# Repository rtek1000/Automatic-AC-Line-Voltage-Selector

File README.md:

# Automatic-AC-Line-Voltage-Selector
Automatic selector for 110VAC or 220VAC

- Usable for equipment that works with only 110V (to protect against wrong connection to 220V) or for 110V / 220V devices with manual switch selection.
- - It can operate with only 1 relay, but the 47V zener diode (D4, D5) must be kept in the scheme so as not to force the MOSFET (Q2).
-
- Operating mode is simple: the normally closed contact (NC) is for higher voltage connection (220V), when the AC line voltage is about 140Vac or less, the relay is activated.
- - The circuit has no hysteresis, so it may oscillate if the AC line voltage is at the threshold.
-
- Note: The wire colors in the example are merely illustrative:

Schematic:

Board:

## Licence:
- Hardware:

Released under CERN OHL 1.2: https://ohwr.org/cernohl

- This library is distributed in the hope that it will be useful, but WITHOUT ANY WARRANTY; without even the implied warranty of MERCHANTABILITY or FITNESS FOR A PARTICULAR PURPOSE.

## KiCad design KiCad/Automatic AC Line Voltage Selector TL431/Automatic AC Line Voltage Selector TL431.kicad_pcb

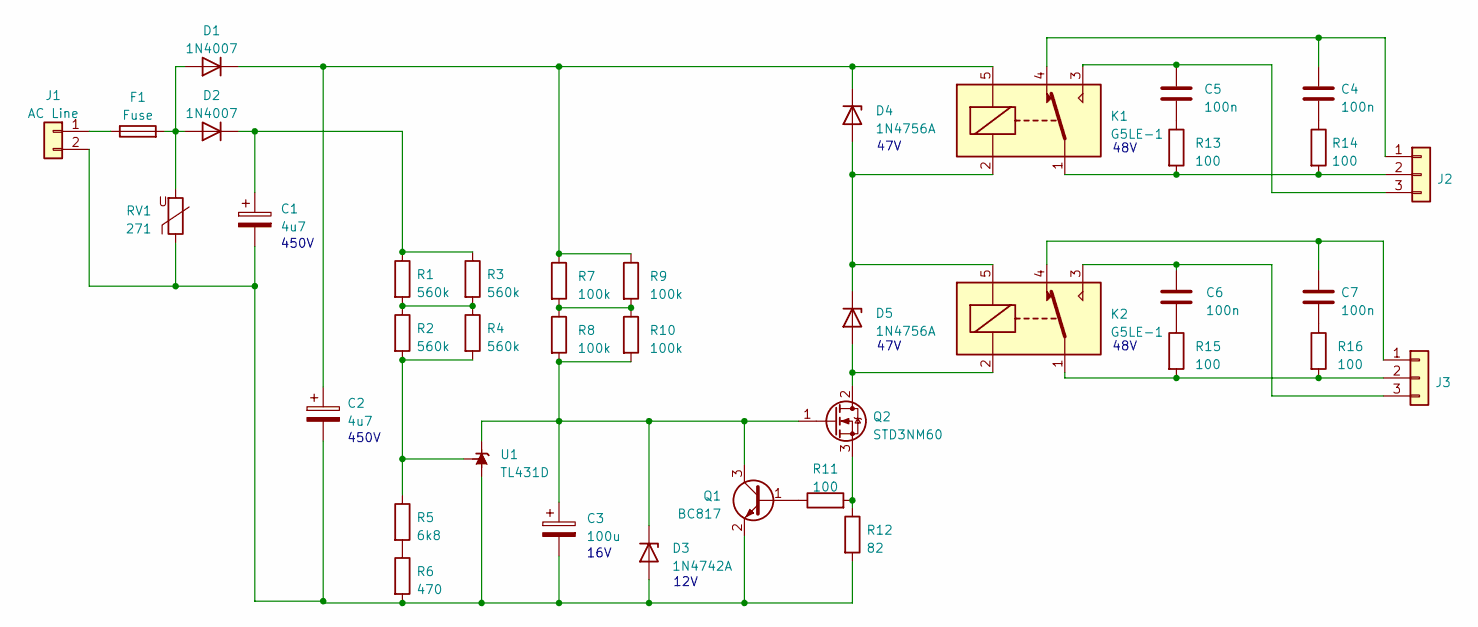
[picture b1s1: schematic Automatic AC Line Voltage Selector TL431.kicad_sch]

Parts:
C1, C2: 4u7; CP_Radial_D10.0mm_P5.00mm
C3: 100u; CP_Radial_D10.0mm_P2.50mm
C4, C5, C6, C7: 100n; C_1812_4532Metric
D1, D2: 1N4007; D_DO-41_SOD81_P7.62mm_Horizontal
D3: 1N4742A; D_DO-41_SOD81_P10.16mm_Horizontal
D4, D5: 1N4756A; D_DO-41_SOD81_P10.16mm_Horizontal
F1: Fuse; Fuseholder_TR5_Littelfuse_No560_No460
J1: AC Line; TE_826576-2_1x02_P3.96mm_Vertical
J2, J3: Conn_01x03; TE_826576-3_1x03_P3.96mm_Vertical
K1, K2: G5LE-1; Relay_SPDT_Omron-G5LE-1
Q1: BC817; SOT-23
Q2: STD3NM60; TO-252-2
R1, R2, R3, R4: 560k; R_2512_6332Metric_Pad1.40x3.35mm_HandSolder
R5: 6k8; R_1206_3216Metric_Pad1.30x1.75mm_HandSolder
R6: 470; R_1206_3216Metric_Pad1.30x1.75mm_HandSolder
R7, R8, R9, R10: 100k; R_2512_6332Metric_Pad1.40x3.35mm_HandSolder
R11, R13, R14, R15, R16: 100; R_1206_3216Metric_Pad1.30x1.75mm_HandSolder
R12: 82; R_1206_3216Metric_Pad1.30x1.75mm_HandSolder
RV1: 271; RV_Disc_D9mm_W6.1mm_P5mm
U1: TL431D; SOIC-8_3.9x4.9mm_P1.27mm

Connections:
unnamed: C4.2, R14.1
unnamed: C5.2, R13.1
unnamed: C6.2, R15.1
unnamed: C7.2, R16.1
unnamed: D1.2 (A), D2.2 (A), F1.2, RV1.2
unnamed: C2.1, D1.1 (K), D4.1 (K), K1.5, R7.1, R9.1
unnamed: C1.1, D2.1 (K), R1.1, R3.1
unnamed: C1.2, C2.2, C3.2, D3.2 (A), J1.2, Q1.2 (E), R6.2, R12.2, RV1.1, U1.2 (A), U1.3 (A), U1.6 (A), U1.7 (A)
unnamed: C3.1, D3.1 (K), Q1.3 (C), Q2.1 (G), R8.2, R10.2, U1.1 (K)
unnamed: D4.2 (A), D5.1 (K), K1.2, K2.5
unnamed: D5.2 (A), K2.2, Q2.2 (D)
unnamed: F1.1, J1.1
unnamed: C4.1, J2.1, K1.4
unnamed: J2.2, K1.1, R13.2, R14.2
unnamed: C5.1, J2.3, K1.3
unnamed: C7.1, J3.1, K2.4
unnamed: J3.2, K2.1, R15.2, R16.2
unnamed: C6.1, J3.3, K2.3
unnamed: Q1.1 (B), R11.1
unnamed: Q2.3 (S), R11.2, R12.1
unnamed: R1.2, R2.1, R3.2, R4.1
unnamed: R5.2, R6.1
unnamed: R7.2, R8.1, R9.2, R10.1
unnamed: R2.2, R4.2, R5.1, U1.8 (REF)

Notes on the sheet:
48V
47V
450V
16V
12V

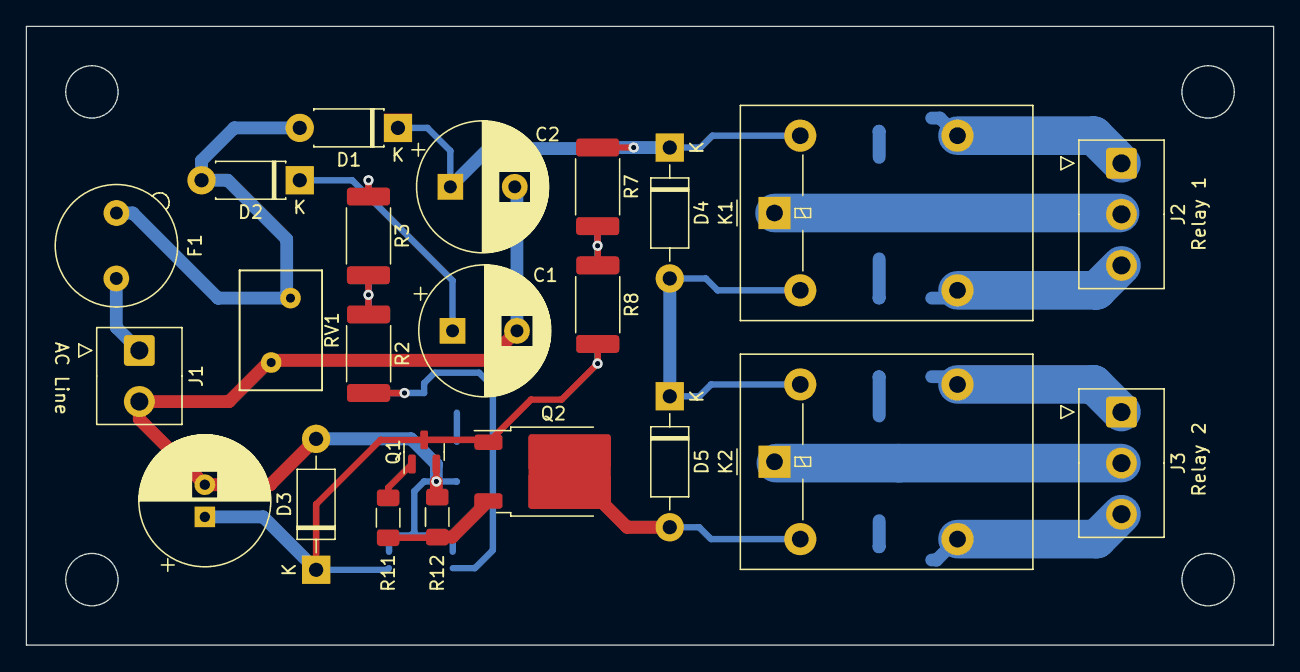
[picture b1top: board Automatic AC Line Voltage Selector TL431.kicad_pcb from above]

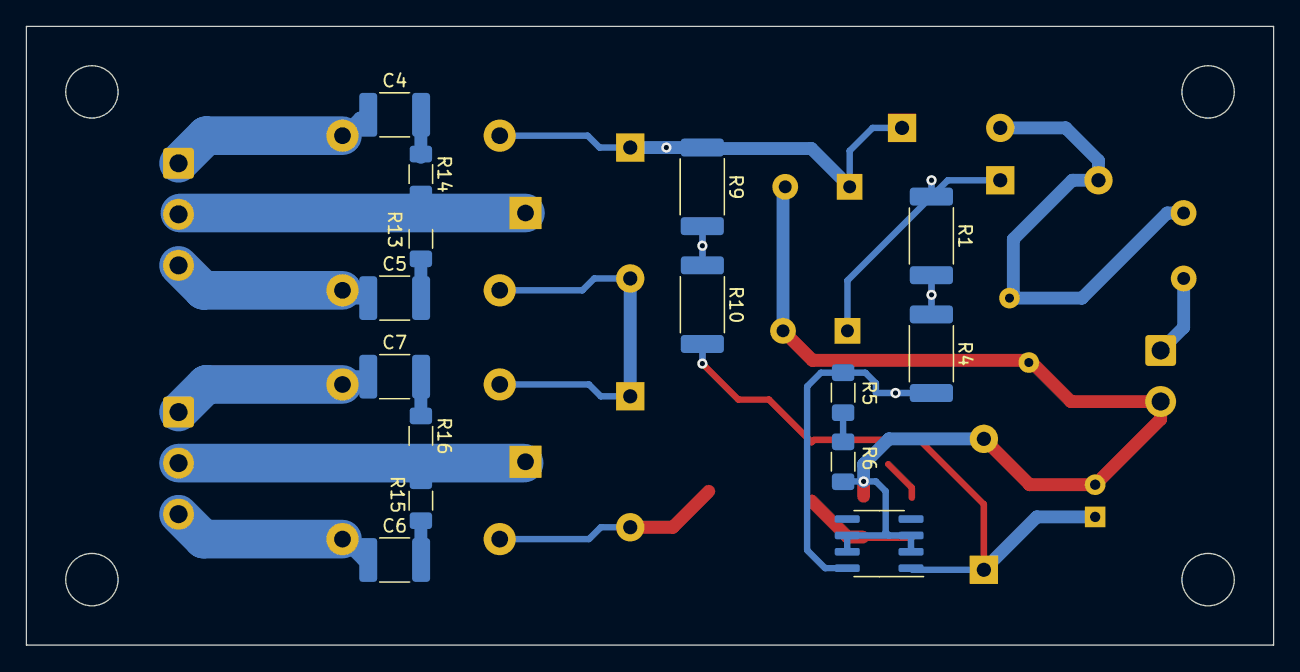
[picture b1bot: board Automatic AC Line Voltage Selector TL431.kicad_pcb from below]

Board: 2 copper layers, 96.8 x 48.0 mm, 38 parts (15 on the bottom side), 24 nets.

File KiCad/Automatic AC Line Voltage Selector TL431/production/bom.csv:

Designator,Footprint,Quantity,Value,LCSC Part #
"C1, C2",CP_Radial_D10.0mm_P5.00mm,2,4u7,
C3,CP_Radial_D10.0mm_P2.50mm,1,100u,
"C4, C5, C6, C7",1812,4,100n,
"D1, D2",D_DO-41_SOD81_P7.62mm_Horizontal,2,1N4007,
D3,D_DO-41_SOD81_P10.16mm_Horizontal,1,1N4742A,
"D4, D5",D_DO-41_SOD81_P10.16mm_Horizontal,2,1N4756A,
F1,Fuseholder_TR5_Littelfuse_No560_No460,1,Fuse,
J1,TE_826576-2_1x02_P3.96mm_Vertical,1,AC Line,
"J2, J3",TE_826576-3_1x03_P3.96mm_Vertical,2,Conn_01x03,
"K1, K2",Relay_SPDT_Omron-G5LE-1,2,G5LE-1,
Q1,SOT-23,1,BC817,
Q2,TO-252-2,1,STD3NM60,
"R1, R2, R3, R4",2512,4,560k,
"R10, R7, R8, R9",2512,4,100k,
"R11, R13, R14, R15, R16",1206,5,100,
R12,1206,1,82,
R5,1206,1,6k8,
R6,1206,1,470,
RV1,RV_Disc_D9mm_W6.1mm_P5mm,1,271,
U1,SOIC-8_3.9x4.9mm_P1.27mm,1,TL431D,
